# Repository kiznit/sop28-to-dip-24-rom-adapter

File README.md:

# sop28-to-dip-24-rom-adapter
ROM adapter board from sop-28 to dip-24.

I recently acquired a Color Computer 1 (CoCo 1) that came with Color Basic 1.1 and no Extended Color Basic. The CoCo 1 I have has the revision E motherboard. It contains two 24-PIN sockets next to each other for the Color Basic (CB) and Extended Color Basic (ECB) ROMs. These ROMs are extremely difficult to find and so are 24-PIN EPROMs.

I decided to use the 28C64 EEPROMs to upgrade my machine. The main difficulty is that space is extremely limited around the sockets and there is only a 0.2" (5.08 mm) gap between the two sockets. This means that I needed an adapter board that was no more than 0.8" (20.32 mm) wide. The usual DIP-28 to DIP-24 adapters will not fit. The solution was to use a SOP-28 EEPROM instead of a DIP-28 and to design my own adapter.

This adapter as of revision 2B will only work with the 28C64, not the 28C256 or the 27 series. This is because PIN 1 is left unconnected as per the 28C64 specifications and I didn't provide a way to connect that PIN to ground or a pull-up resistor. PIN 26 is grounded but should probably have been left floating. The 4.7K pull-up resistor is used to bring PIN 27 (/WE) high.

The **bin** folder contains a zip file that can be uploaded directly to JLBPCB for production.

Revision 2B is the same as revision 2 but with a smaller footprint.

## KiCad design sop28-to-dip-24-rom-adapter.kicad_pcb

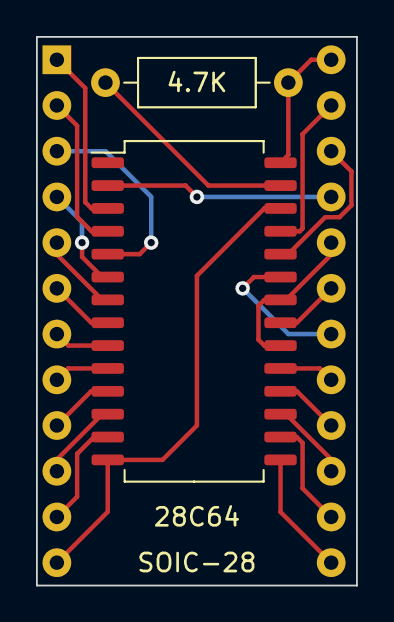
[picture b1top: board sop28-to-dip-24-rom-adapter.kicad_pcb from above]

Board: 2 copper layers, 17.8 x 30.5 mm, 3 parts (0 on the bottom side), 25 nets.

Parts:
4.7K: 4.7K; R_Axial_DIN0207_L6.3mm_D2.5mm_P10.16mm_Horizontal
28C64: EPROM_28; SOIC-28W_7.5x18.7mm_P1.27mm
U2: ROM_24; DIP-24_W15.24mm-Notch

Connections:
/A0: 28C64.10 (A0), U2.8 (A0)
/A1: 28C64.9 (A1), U2.7 (A1)
/A2: 28C64.8 (A2), U2.6 (A2)
/A3: 28C64.7 (A3), U2.5 (A3)
/A4: 28C64.6 (A4), U2.4 (A4)
/A5: 28C64.5 (A5), U2.3 (A5)
/A6: 28C64.4 (A6), U2.2 (A6)
/A7: 28C64.3 (A7), U2.1 (A7)
/A8: 28C64.25 (A8), U2.23 (A8)
/A9: 28C64.24 (A9), U2.22 (A9)
/A10: 28C64.21 (A10), U2.19 (A10)
/A11: 28C64.23 (A11), U2.18 (A11)
/A12: 28C64.2 (A12), U2.21 (A12)
/D0: 28C64.11 (D0), U2.9 (D0)
/D1: 28C64.12 (D1), U2.10 (D1)
/D2: 28C64.13 (D2), U2.11 (D2)
/D3: 28C64.15 (D3), U2.13 (D3)
/D4: 28C64.16 (D4), U2.14 (D4)
/D5: 28C64.17 (D5), U2.15 (D5)
/D6: 28C64.18 (D6), U2.16 (D6)
/D7: 28C64.19 (D7), U2.17 (D7)
GND: 28C64.14 (GND), 28C64.26, U2.12 (GND)
unnamed: 28C64.20 (~CS), 28C64.22 (~OE), U2.20 (~CE)
unnamed: 4.7K.2, 28C64.27 (~WE)
VCC: 4.7K.1, 28C64.28 (VCC), U2.24 (VCC)

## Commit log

2024-04-15 Revision 2.
2024-04-15 README update.
2024-04-15 Remove lock file.
2024-04-15 Revision 3.
2024-04-24 Revision 2B.
